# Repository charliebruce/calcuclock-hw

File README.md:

# calcuclock-hw
PCB and schematic for the calcuclock project. The firmware for this hardware can be found at https://github.com/charliebruce/calcuclock-sw

This PCB can be purchased through OSHPark: https://oshpark.com/shared_projects/vCfoimMo

# License
Released under the CC BY-NC-SA 3.0 license.

For more details see a summary at:
https://creativecommons.org/licenses/by-nc-sa/3.0/ 
and the accompanying legal text:
https://creativecommons.org/licenses/by-nc-sa/3.0/legalcode

Please raise an issue or send me an email if you wish to use this project commercially.

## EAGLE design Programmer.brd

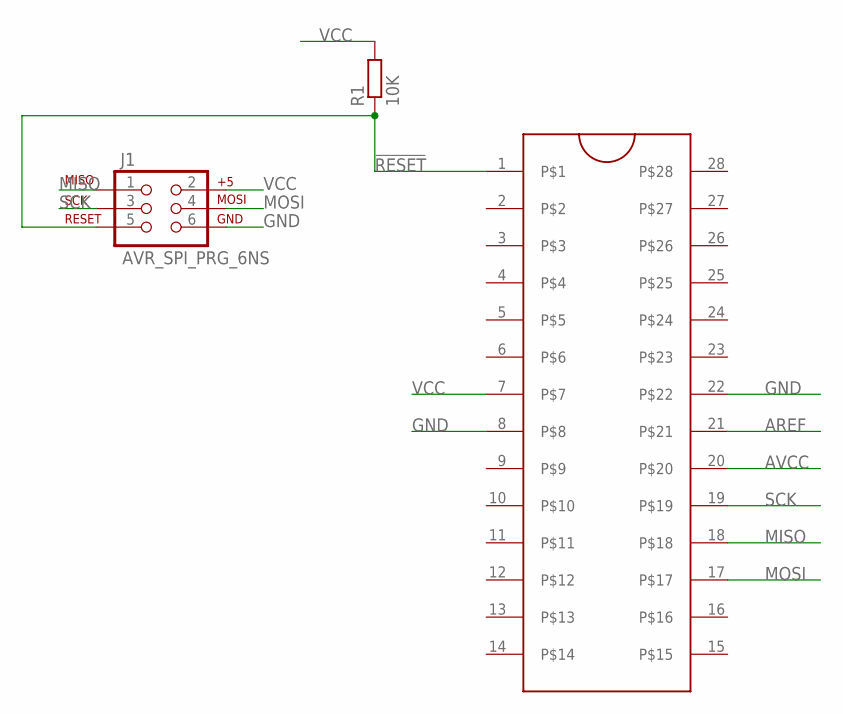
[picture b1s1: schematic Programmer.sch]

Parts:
J1: AVR_SPI_PRG_6NS; 2X3-NS
R1: 10K; 0207/10
U$1: ZIFSOCKET-28-3ZIFFSOCKET-28-3; DIL28-3-ZIF_SOCKET

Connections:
!RESET!: J1.5, R1.1, U$1.1
AREF: U$1.21
AVCC: U$1.20
GND: J1.6, U$1.8, U$1.22
MISO: J1.1, U$1.18
MOSI: J1.4, U$1.17
SCK: J1.3, U$1.19
VCC: J1.2, R1.2, U$1.7

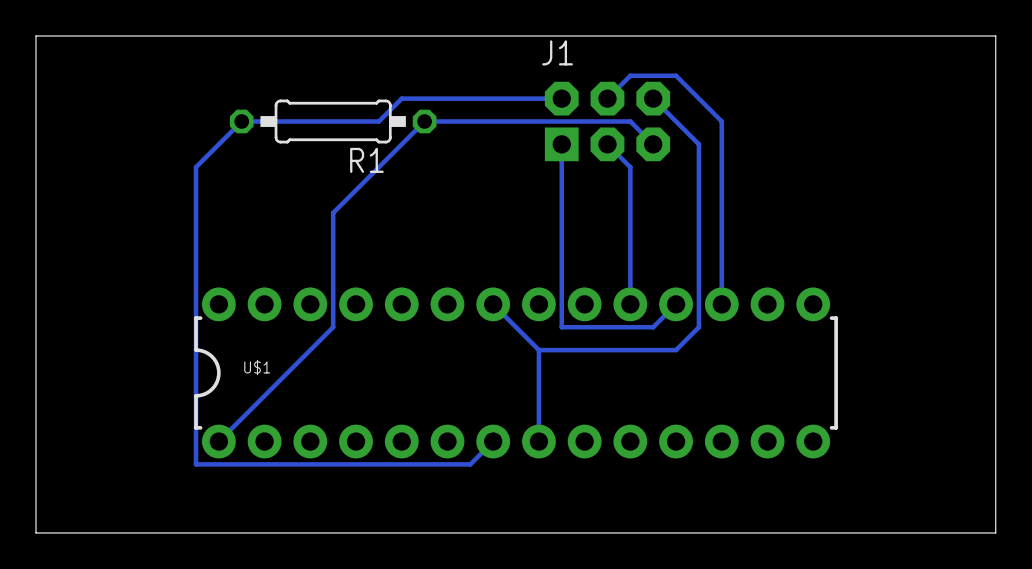
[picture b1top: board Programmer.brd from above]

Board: 2 copper layers, 53.3 x 27.6 mm, 3 parts (0 on the bottom side), 6 nets.

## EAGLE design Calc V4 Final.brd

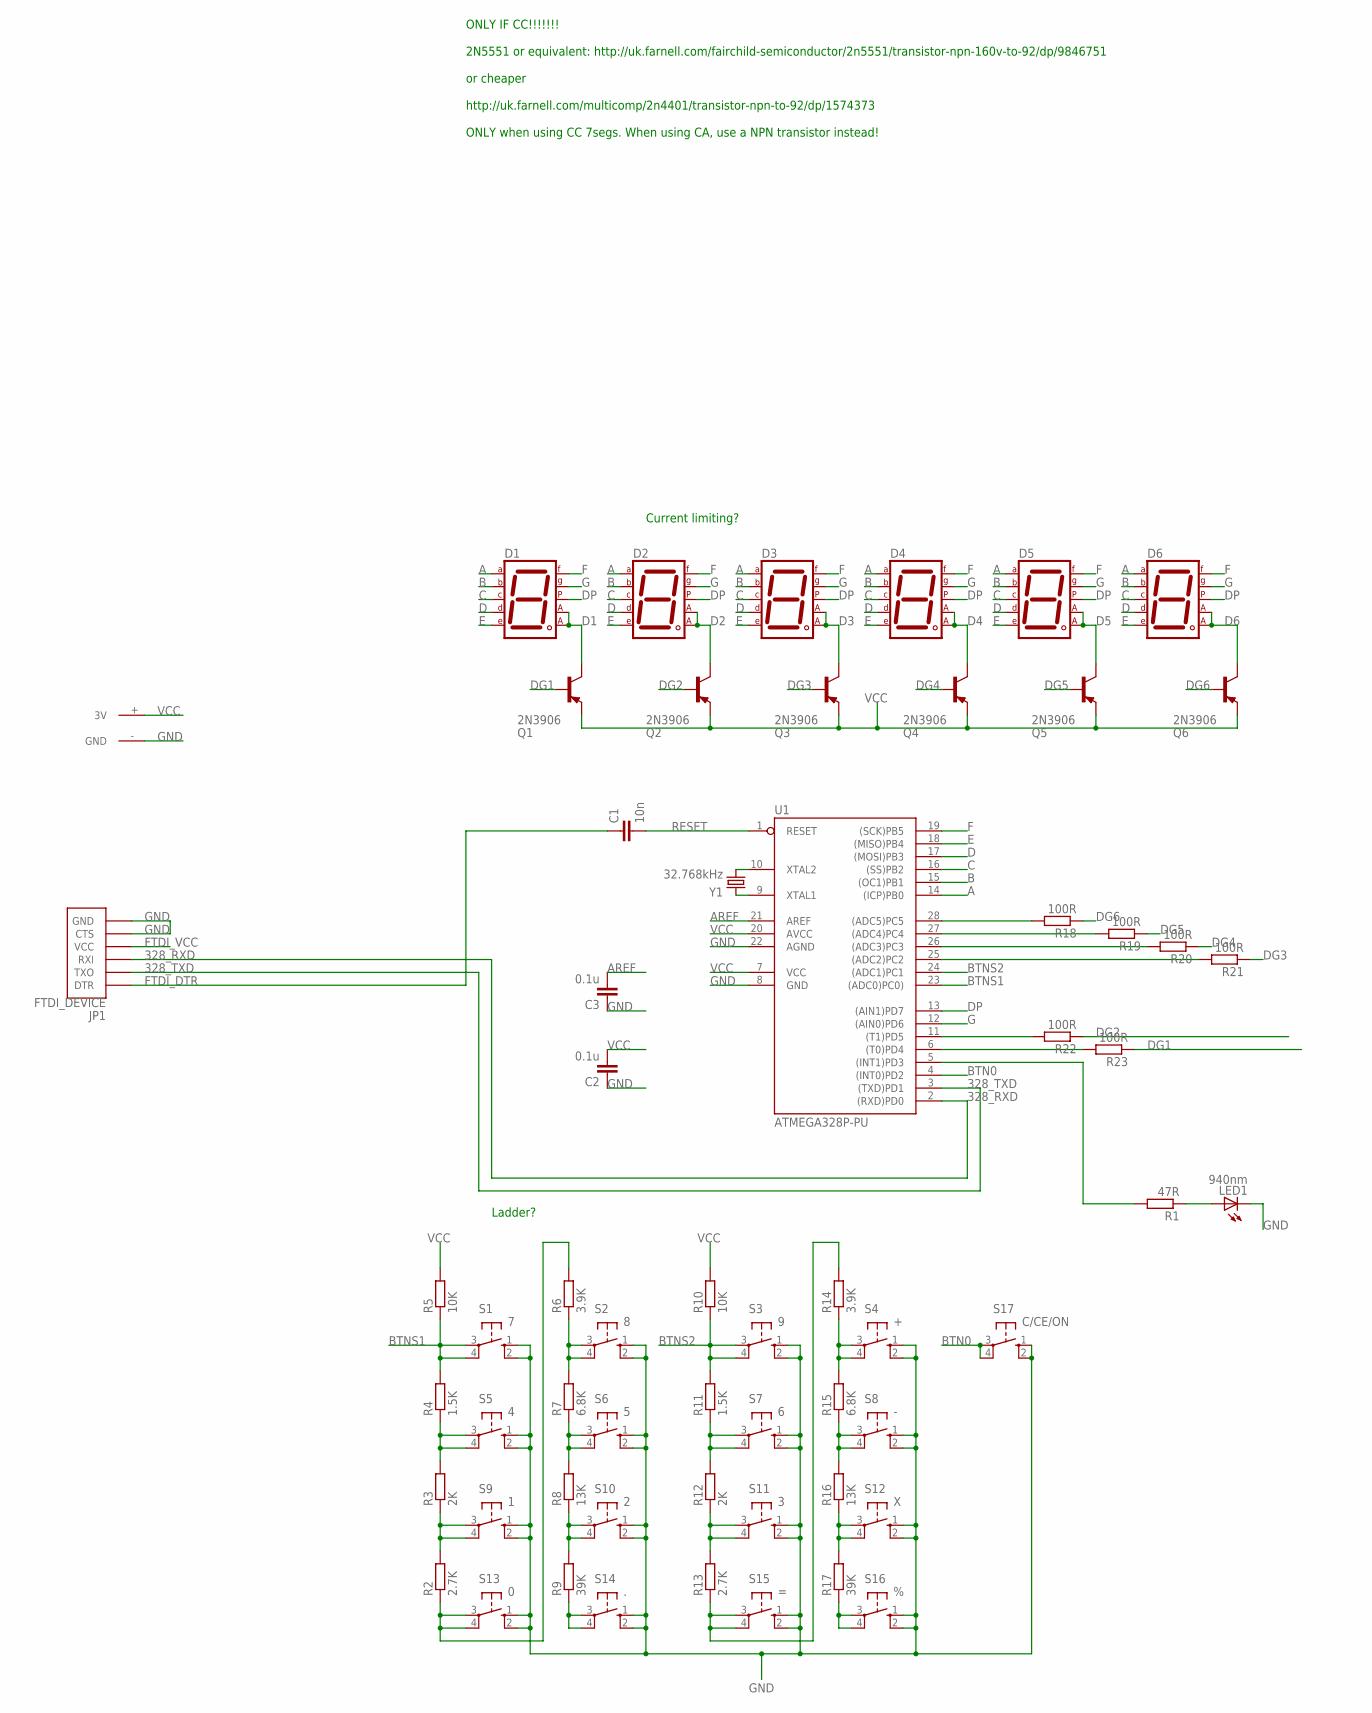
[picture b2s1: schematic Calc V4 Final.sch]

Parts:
C1: 10n; C025-024X044
C2, C3: 0.1u; C025-024X044
D1, D2, D3, D4, D5, D6: 7SEG-MCA; 7SEG-7
JP1: FTDI_DEVICE; FTDI_DEVICE_SIDE
LED1: 940nm; LED5MM
Q1, Q2, Q3, Q4, Q5, Q6: 2N3906; TO92
R1: 47R; 0207/10
R2, R13: 2.7K; 0207/10
R3, R12: 2K; 0207/10
R4, R11: 1.5K; 0207/10
R5, R10: 10K; 0207/10
R6, R14: 3.9K; 0207/10
R7, R15: 6.8K; 0207/10
R8, R16: 13K; 0207/10
R9, R17: 39K; 0207/10
R18, R19, R20, R21, R22, R23: 100R; 0207/7
S1: 7; B3F-10XX
S2: 8; B3F-10XX; MPN B3F-1000
S3: 9; B3F-10XX; MPN B3F-1000
S4: +; B3F-10XX; MPN B3F-1000
S5: 4; B3F-10XX; MPN B3F-1000
S6: 5; B3F-10XX; MPN B3F-1000
S7: 6; B3F-10XX; MPN B3F-1000
S8: -; B3F-10XX; MPN B3F-1000
S9: 1; B3F-10XX
S10: 2; B3F-10XX; MPN B3F-1000
S11: 3; B3F-10XX; MPN B3F-1000
S12: X; B3F-10XX; MPN B3F-1000
S13: 0; B3F-10XX; MPN B3F-1000
S14: .; B3F-10XX; MPN B3F-1000
S15: =; B3F-10XX; MPN B3F-1000
S16: %; B3F-10XX; MPN B3F-1000
S17: C/CE/ON; B3F-10XX; MPN B3F-1000
U1: ATMEGA328P-PU; DIL28-3
U$1: AAA-BATTERY; AAA-BATTERY-CONTACT
Y1: 32.768kHz; TC26HEZ

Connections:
328_RXD: JP1.P$3 (RXI), U1.2 ((RXD)PD0)
328_TXD: JP1.P$2 (TXO), U1.3 ((TXD)PD1)
A: D1.10 (A), D2.10 (A), D3.10 (A), D4.10 (A), D5.10 (A), D6.10 (A), U1.14 ((ICP)PB0)
AREF: C3.2, U1.21 (AREF)
B: D1.9 (B), D2.9 (B), D3.9 (B), D4.9 (B), D5.9 (B), D6.9 (B), U1.15 ((OC1)PB1)
BTN0: S17.3, S17.4 (P1), U1.4 ((INT0)PD2)
BTNS1: R4.2, R5.1, S1.3, S1.4 (P1), U1.23 ((ADC0)PC0))
BTNS2: R10.1, R11.2, S3.3, S3.4 (P1), U1.24 ((ADC1)PC1)
C: D1.8 (C), D2.8 (C), D3.8 (C), D4.8 (C), D5.8 (C), D6.8 (C), U1.16 ((SS)PB2)
D: D1.5 (D), D2.5 (D), D3.5 (D), D4.5 (D), D5.5 (D), D6.5 (D), U1.17 ((MOSI)PB3)
D1: D1.1 (CA1), D1.6 (CA2), Q1.1 (C)
D2: D2.1 (CA1), D2.6 (CA2), Q2.1 (C)
D3: D3.1 (CA1), D3.6 (CA2), Q3.1 (C)
D4: D4.1 (CA1), D4.6 (CA2), Q4.1 (C)
D5: D5.1 (CA1), D5.6 (CA2), Q5.1 (C)
D6: D6.1 (CA1), D6.6 (CA2), Q6.1 (C)
DG1: Q1.2 (B), R23.1
DG2: Q2.2 (B), R22.1
DG3: Q3.2 (B), R21.1
DG4: Q4.2 (B), R20.1
DG5: Q5.2 (B), R19.1
DG6: Q6.2 (B), R18.1
DP: D1.7 (DP), D2.7 (DP), D3.7 (DP), D4.7 (DP), D5.7 (DP), D6.7 (DP), U1.13 ((AIN1)PD7)
E: D1.4 (E), D2.4 (E), D3.4 (E), D4.4 (E), D5.4 (E), D6.4 (E), U1.18 ((MISO)PB4)
F: D1.2 (F), D2.2 (F), D3.2 (F), D4.2 (F), D5.2 (F), D6.2 (F), U1.19 ((SCK)PB5)
FTDI_DTR: C1.1, JP1.P$1 (DTR)
FTDI_VCC: JP1.P$4 (VCC)
G: D1.3 (G), D2.3 (G), D3.3 (G), D4.3 (G), D5.3 (G), D6.3 (G), U1.12 ((AIN0)PD6)
GND: C2.1, C3.1, JP1.P$5 (CTS), JP1.P$6 (GND), LED1.K (C), S1.1 (S), S1.2 (S1), S2.1 (S), S2.2 (S1), S3.1 (S), S3.2 (S1), S4.1 (S), S4.2 (S1), S5.1 (S), S5.2 (S1), S6.1 (S), S6.2 (S1), S7.1 (S), S7.2 (S1), S8.1 (S), S8.2 (S1), S9.1 (S), S9.2 (S1), S10.1 (S), S10.2 (S1), S11.1 (S), S11.2 (S1), S12.1 (S), S12.2 (S1), S13.1 (S), S13.2 (S1), S14.1 (S), S14.2 (S1), S15.1 (S), S15.2 (S1), S16.1 (S), S16.2 (S1), S17.1 (S), S17.2 (S1), U1.8 (GND), U1.22 (AGND), U$1.- (GND)
unnamed: LED1.A, R1.1
unnamed: R1.2, U1.5 ((INT1)PD3)
unnamed: R2.1, R6.2, S13.3, S13.4 (P1)
unnamed: R2.2, R3.1, S9.3, S9.4 (P1)
unnamed: R3.2, R4.1, S5.3, S5.4 (P1)
unnamed: R6.1, R7.2, S2.3, S2.4 (P1)
unnamed: R9.1, S14.3, S14.4 (P1)
unnamed: R8.1, R9.2, S10.3, S10.4 (P1)
unnamed: R7.1, R8.2, S6.3, S6.4 (P1)
unnamed: R18.2, U1.28 ((ADC5)PC5)
unnamed: R11.1, R12.2, S7.3, S7.4 (P1)
unnamed: R13.1, R14.2, S15.3, S15.4 (P1)
unnamed: R12.1, R13.2, S11.3, S11.4 (P1)
unnamed: R17.1, S16.3, S16.4 (P1)
unnamed: R16.1, R17.2, S12.3, S12.4 (P1)
unnamed: R15.1, R16.2, S8.3, S8.4 (P1)
unnamed: R14.1, R15.2, S4.3, S4.4 (P1)
unnamed: R19.2, U1.27 ((ADC4)PC4)
unnamed: R20.2, U1.26 ((ADC3)PC3)
unnamed: R21.2, U1.25 ((ADC2)PC2)
unnamed: R22.2, U1.11 ((T1)PD5)
unnamed: R23.2, U1.6 ((T0)PD4)
RESET: C1.2, U1.1 (RESET)
VCC: C2.2, Q1.3 (E), Q2.3 (E), Q3.3 (E), Q4.3 (E), Q5.3 (E), Q6.3 (E), R5.2, R10.2, U1.7 (VCC), U1.20 (AVCC), U$1.+ (3V)
XTAL_N: U1.9 (XTAL1), Y1.2
XTAL_P: U1.10 (XTAL2), Y1.1

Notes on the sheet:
Ladder?
Current limiting?
ONLY IF CC!!!!!!! 2N5551 or equivalent: http://uk.farnell.com/fairchild-semiconductor/2n5551/transistor-npn-160v-to-92/dp/9846751 or cheaper http://uk.farnell.com/multicomp/2n4401/transistor-npn-to-92/dp/1574373 ONLY when using CC 7segs. When using CA, use a NPN transistor instead!

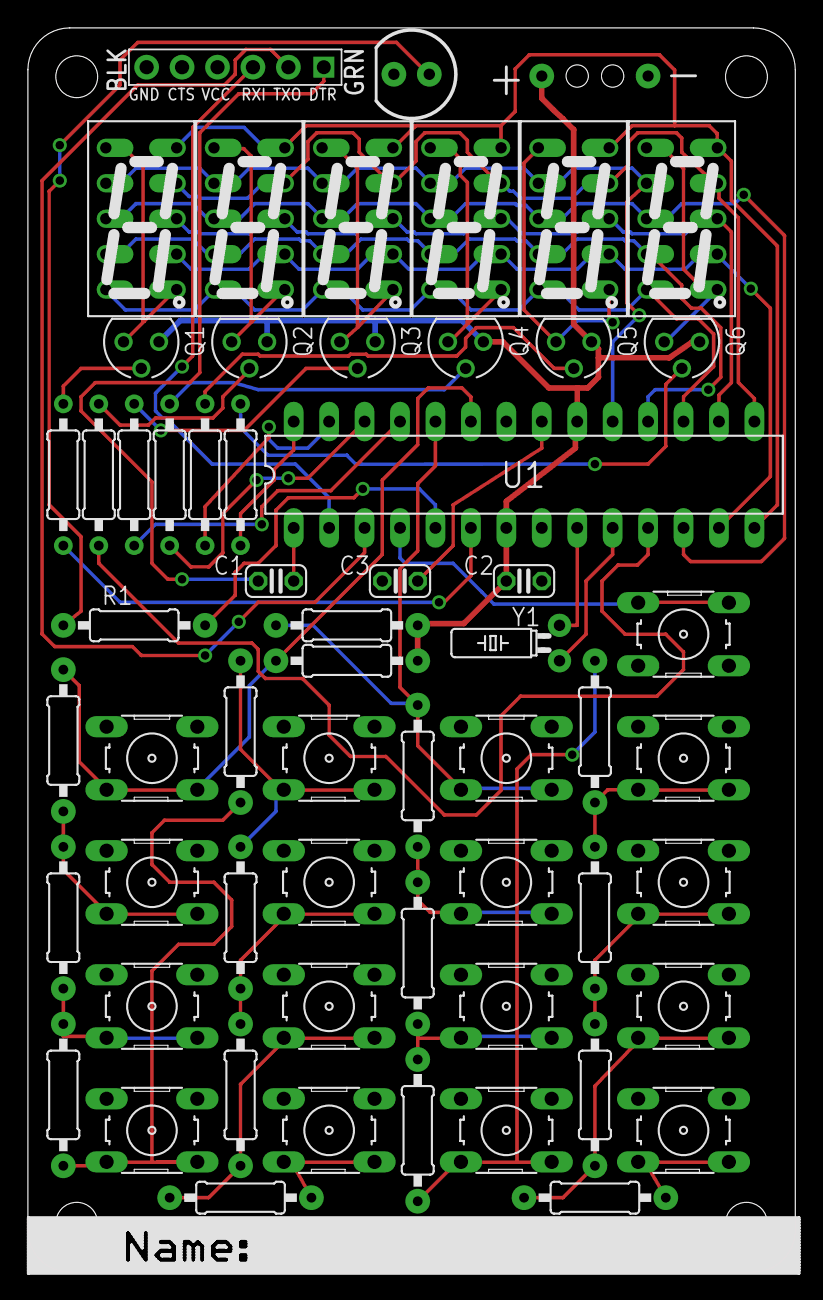
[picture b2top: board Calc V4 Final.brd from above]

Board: 2 copper layers, 55.0 x 89.2 mm, 60 parts (0 on the bottom side), 54 nets.

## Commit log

2015-09-05 Initial commit of calcuclock PCB design.
2015-09-05 Add assembly guide.
2017-05-15 Add board render
2017-05-15 Add BoM
2017-05-15 Add a programming tool board, allows chips to be programmed using AVRISP and a ZIF socket or similar.

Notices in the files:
parts and their libraries:
SparkFun-Connectors: Licensing: CC v3.0 Share-Alike You are welcome to use this library for commercial purposes.
